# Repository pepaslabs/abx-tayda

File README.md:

# abx-tayda

A relay board for performing blind A/B testing of two audio sources.

This version of the board is designed around parts available from [Tayda electronics](https://www.taydaelectronics.com/).

See the thread at [diyaudio.com](https://www.diyaudio.com/forums/equipment-and-tools/361743-abx-box.html).

This board design is open source hardware, released under the terms of the [MIT license](https://opensource.org/licenses/MIT).  It requires an [ancient version of Kicad](https://archive.org/details/2013-kicad) (sorry, not sorry 😝).  Debian users will need to add a jessie source to install the libpng12 dependency.

## v4.1 release

[schematic](releases/v4.1/abx.pdf)

[gerbers.zip](releases/v4.1/gerbers.zip)

[firmware](https://github.com/pepaslabs/abx-tayda/blob/main/releases/v4.1/firmware/abx/abx.ino)

Changes from v4:
- Include missing base resistor R28.

### Bill of materials

- **D4-6**: three 1N5817 Schottky diodes.
  - Any diode will work, but the lower voltage drop of Schottky diodes extracts more useful life from the 9V battery.
  - [Tayda](https://www.taydaelectronics.com/1n5817-diode-schottky-1a-20v.html)
- **D7-10**: four LED's.
  - Any color.  3mm or 5mm.
  - [Tayda](https://www.taydaelectronics.com/leds/round-leds/5mm-leds/led-5mm-red.html)
- **D11-22**: twelve 1N4148 diodes.
  - Flyback diodes.  Any diode will work here.
  - [Tayda](https://www.taydaelectronics.com/1n4148-switching-signal-diode.html)
- **R1-4**: four 220R 1/4 watt resistors.
  - LED current limiting.  Tune the resistance value to get the LED brightness you prefer.
  - [Tayda](https://www.taydaelectronics.com/resistors/1-4w-metal-film-resistors/resistor-220-ohm-1-4w-1-metal-film-pkg-of-10.html)
- **R5-7,20-22**: six 100k 1/4 watt resistors.
  - Voltage dividers for Arduino inputs.  5% carbon film or 1% metal film.
  - [Tayda](https://www.taydaelectronics.com/resistors/1-4w-metal-film-resistors/10-x-resistor-100k-ohm-1-4w-1-metal-film-pkg-of-10.html)
- **R8-19**: twelve 100k 1/4 watt resistors.
  - MOSFET gate pull-up and pull-down resistors.  5% carbon film or 1% metal film.
  - [Tayda](https://www.taydaelectronics.com/resistors/1-4w-metal-film-resistors/10-x-resistor-100k-ohm-1-4w-1-metal-film-pkg-of-10.html)
- **R23-27**: six 10k 1/4 watt resistors.
  - PNP base current-limiting resistors.  5% carbon film or 1% metal film.
  - [Tayda](https://www.taydaelectronics.com/resistors/1-4w-metal-film-resistors/10-x-resistor-10k-ohm-1-4w-1-metal-film-pkg-of-10.html)
- **SW1-3**: three miniature micro switches.
  - Tayda [MX1382-F91](https://www.taydaelectronics.com/mx1382-f91-micro-switch-1p2t-1a-mx1382-f91.html)
- **Q1,3,5,7,9,11**: six 2N3906 PNP BJT transistors.
  - [Tayda](https://www.taydaelectronics.com/2n3906-general-propose-pnp-transistor.html)
  - Any TO-92 PNP transistor which can handle 100mA (with an EBC pinout) will work fine.
- **Q2,4,6,8,10,12**: six 2N7000 N-channel MOSFETs.
  - [Tayda](https://www.taydaelectronics.com/2n7000-mosfet-n-channel-60v-0-2a.html)
  - Any TO-92 N-channel MOSFET which can handle 100mA (with an SGD pinout) will work fine.
- **K1-6**: six 3V latching relays
  - Tayda [FTR-B3GB003Z](https://www.taydaelectronics.com/ftr-b3gb003z-b10-mini-relay-dpdt-3vdc-1a.html)
- **CON1-3**: three 3.5mm headphone jacks
  - Tayda [PJ-307](https://www.taydaelectronics.com/3-5mm-stereo-enclosed-socket-chassis-jack.html)
  - Digikey [SJ1-3523N](https://www.digikey.com/en/products/detail/cui-devices/SJ1-3523N/738689)
- **IC1**: one Arduino Nano board.
  - Any $5 Arduino Nano board on ebay will work fine.

Choose one:
- **CON4**: 2.1x5.5mm DC barrel jack
  - [Tayda](https://www.taydaelectronics.com/dc-power-jack-2-1mm-barrel-type-pcb-mount.html)
  - [Tayda](https://www.taydaelectronics.com/9v-9-volt-battery-clip-connector-with-barrel-jack-plug.html)
  - [Tayda](https://www.taydaelectronics.com/9v-battery-holder-with-barrel-jack-plug.html)
- **P1**: 9V battery pigtail

## v4 release

[schematic](releases/v4/abx.pdf)

[gerbers.zip](releases/v4/gerbers.zip)

[firmware](https://github.com/pepaslabs/abx-tayda/blob/main/releases/v4/firmware/abx/abx.ino)

Changes from v3:
- Use 2N3906 PNP BJT's which are cheaper than BS250 P-channel MOSFETs (and are available from tayda)
- Use wider traces for the signal path.

## v3 release

[schematic](releases/v3/abx.pdf)

[gerbers.zip](releases/v3/gerbers.zip)

[firmware](https://github.com/pepaslabs/abx-tayda/blob/main/releases/v3/firmware/abx/abx.ino)

Changes from v2:
- Add test points to input X and Y for volume matching convenience.
- Use pins RX0, TX1 instead of A6, A7 (which cannot be used a digital outputs).

## v2 release

This release fixes a couple of bugs from v1:
- Replaced the 100k input resistors with proper voltage dividers.
- Fixed the silkscreen outline of the relays.

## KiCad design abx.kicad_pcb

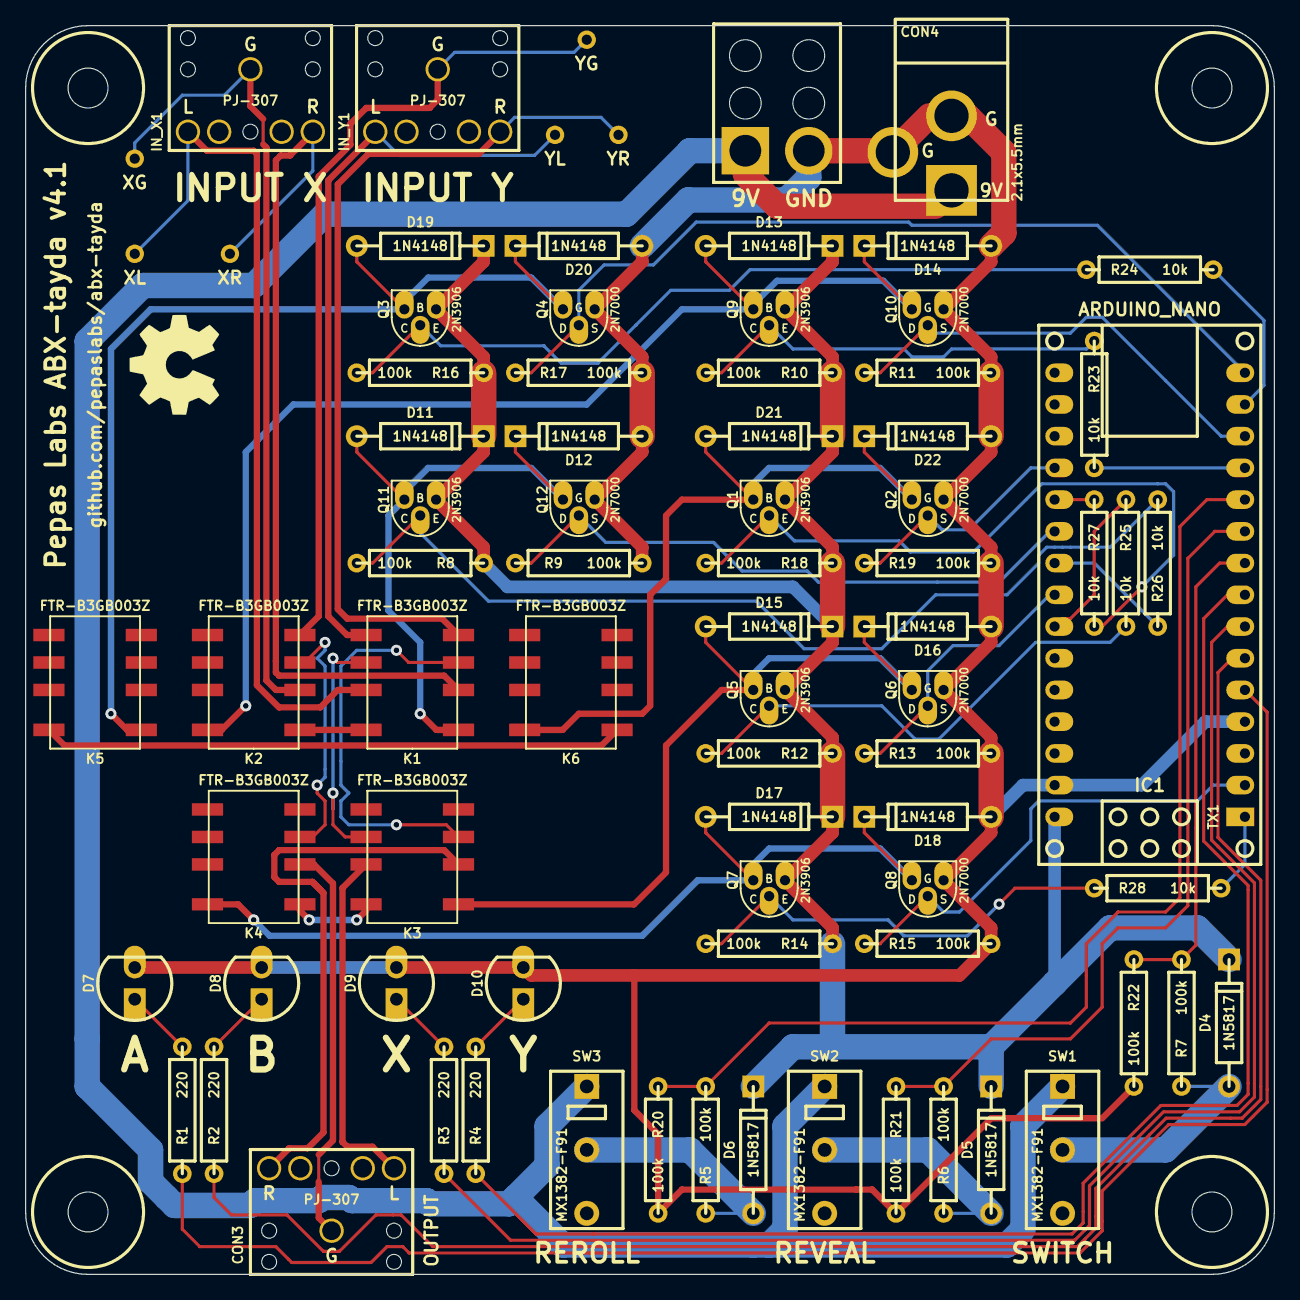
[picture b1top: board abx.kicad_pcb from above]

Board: 2 copper layers, 100.0 x 100.0 mm, 84 parts (0 on the bottom side), 56 nets.

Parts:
CON3: PJ-307; SJ1-3523N
CON4: 2.1x5.5mm; BARREL_JACK_21x55
D4, D5, D6: 1N5817; DIODE_1A_069A_04_PL
D7: LEDA; LED_5MM
D8: LEDB; LED_5MM
D9: LEDX; LED_5MM
D10: LEDY; LED_5MM
D11, D12, D13, D14, D15, D16, D17, D18, D19, D20, D21, D22: 1N4148; DIODE_1A_069A_04_PL
H***: Val**; hole_M3_NPTH
H***#2, H***#3, H***#4: Val**; hole_M3_NPTH
IC1: ARDUINO_NANO; ARDUINO_NANO_PL
IN_X1: PJ-307; SJ1-3523N
IN_Y1: PJ-307; SJ1-3523N
K1, K2, K3, K4, K5, K6: FTR-B3GB003Z; FTR-B3G
P1: CONN_2X1; PIGTAIL2
P2: YL; 1pin_032_058
P3: YR; 1pin_032_058
P4: YG; 1pin_032_058
P5: XL; 1pin_032_058
P6: XR; 1pin_032_058
P7: XG; 1pin_032_058
Q1, Q3, Q5, Q7, Q9, Q11: 2N3906; TO-92_Q_EBC_059Bo_PL
Q2, Q4, Q6, Q8, Q10, Q12: 2N7000; TO-92_Q_SGD_059Bo_PL
R1, R2, R3, R4: 220; R_AXIAL_0W25_059A_PL
R5, R6, R7, R8, R9, R10, R11, R12, R13, R14, R15, R16, R17, R18, R19, R20, R21, R22: 100k; R_AXIAL_0W25_059A_PL
R23, R24, R25, R26, R27, R28: 10k; R_AXIAL_0W25_059A_PL
SW1: SWITCH; MX1382-F91
SW2: REVEAL; MX1382-F91
SW3: REROLL; MX1382-F91

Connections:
5V_LEDA: IC1.5, R1.1
5V_LEDB: IC1.6, R2.1
5V_LEDX: IC1.7, R3.1
5V_LEDY: IC1.8, R4.1
7V: D4.2, D5.2, D6.2, D11.2, D13.2, D15.2, D17.2, D19.2, D21.2, IC1.30, Q1.1, Q3.1, Q5.1, Q7.1, Q9.1, Q11.1, R8.1, R10.1, R12.1, R14.1, R16.1, R18.1
8V_REROLL: D6.1, R5.1, SW3.2
8V_REVEAL: D5.1, R6.1, SW2.2
8V_SWITCH: D4.1, R7.1, SW1.2
9V: CON4.1, P1.1, SW1.1, SW2.1, SW3.1
GND: CON4.2, CON4.3, D7.2, D8.2, D9.2, D10.2, D12.1, D14.1, D16.1, D18.1, D20.1, D22.1, IC1.4, IC1.29, P1.2, Q2.1, Q4.1, Q6.1, Q8.1, Q10.1, Q12.1, R9.2, R11.2, R13.2, R15.2, R17.2, R19.2, R20.2, R21.2, R22.2
unnamed: K3.8, K4.1
unnamed: CON3.3, K3.2
unnamed: CON3.1, K4.2
unnamed: IC1.24, R25.1
unnamed: K5.8, K6.1
unnamed: D9.1, R3.2
unnamed: D8.1, R2.2
unnamed: D7.1, R1.2
unnamed: D10.1, R4.2
unnamed: IN_Y1.3, K1.4, P3.1
unnamed: IN_Y1.1, K2.4, P4.1
unnamed: IC1.9, R7.2, R22.1
unnamed: K1.8, K2.1
unnamed: IC1.10, R6.2, R21.1
unnamed: IC1.14, R24.2
unnamed: IC1.12, R23.2
unnamed: IC1.11, R5.2, R20.1
unnamed: IC1.1, R28.2
unnamed: IN_X1.3, K1.2, P6.1
unnamed: IN_X1.2, K1.7, P5.1
unnamed: IN_Y1.2, K1.5, P2.1
unnamed: CON3.2, K3.7
unnamed: IN_X1.1, K2.2, P7.1
unnamed: IC1.22, R26.1
unnamed: IC1.20, R27.1
unnamed: D15.1, D16.2, K3.1, Q5.3, Q6.3
unnamed: D19.1, D20.2, K5.1, Q3.3, Q4.3
unnamed: D21.1, D22.2, K6.8, Q1.3, Q2.3
unnamed: D11.1, D12.2, K1.1, Q11.3, Q12.3
unnamed: D17.1, D18.2, K4.8, Q7.3, Q8.3
unnamed: D13.1, D14.2, K2.8, Q9.3, Q10.3
NCH1: IC1.13, Q10.2, R11.1
NCH2: IC1.21, Q12.2, R9.1
NCH3: IC1.2, Q8.2, R15.1
NCH4: IC1.23, Q6.2, R13.1
NCH5: IC1.19, Q2.2, R19.1
NCH6: IC1.15, Q4.2, R17.1
PNP1: Q11.2, R8.2, R26.2
PNP2: Q9.2, R10.2, R23.1
PNP3: Q5.2, R12.2, R25.2
PNP4: Q7.2, R14.2, R28.1
PNP5: Q3.2, R16.2, R24.1
PNP6: Q1.2, R18.2, R27.2
RING: K1.3, K3.3
SLEEVE: K2.3, K4.3
TIP: K1.6, K3.6

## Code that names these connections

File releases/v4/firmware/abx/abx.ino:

// ABX switch box (tayda version).
// Copyright 2020 Jason Pepas
// Released under the terms of the MIT license.
// See https://opensource.org/licenses/MIT

// Forum thread:
// https://www.diyaudio.com/forums/equipment-and-tools/361743-abx-box.html


#include <EEPROM.h>


// Pin mapping:

#define LED_A 2
#define LED_B 3
#define LED_X 4
#define LED_Y 5

#define PCH1 A3
#define NCH1 10
#define PCH2 9
#define NCH2 A2
#define PCH3 A5
#define NCH3 0
#define PCH4 1
#define NCH4 A4
#define PCH5 11
#define NCH5 A0
#define PCH6 A1
#define NCH6 12

#define MODE_PIN_REROLL 8
#define MODE_PIN_REVEAL 7
#define MODE_PIN_SWITCH 6


// Misc. constants:

#define MAPPING_A_IS_X 101
#define MAPPING_A_IS_Y 102
#define MAPPING_B_IS_X 102
#define MAPPING_B_IS_Y 101

#define POSITION_X 103
#define POSITION_Y 104

#define RELAY_DURATION 4


// Global variables:

byte g_eeprom_initialized;
byte g_random_seed;
byte g_random_seq;
byte g_abxy_mapping;
byte g_input_position;
byte g_dummy_position;


// EEPROM addresses

#define G_EEPROM_INITIALIZED_ADDR 0
#define G_RANDOM_SEED_ADDR 1
#define G_RANDOM_SEQ_ADDR 2
#define G_ABXY_MAPPING_ADDR 3
#define G_INPUT_POSITION_ADDR 4
#define G_DUMMY_POSITION_ADDR 5


// Misc. functions:

void panic() {
    pinMode(LED_A, OUTPUT);
    pinMode(LED_B, OUTPUT);
    while (true) {
        digitalWrite(LED_A, HIGH);
        digitalWrite(LED_B, HIGH);
    }
}


// EEPROM functions

void load_globals_from_eeprom() {
    g_eeprom_initialized = EEPROM.read(G_EEPROM_INITIALIZED_ADDR);
    if (g_eeprom_initialized != 42) {
        // this is the first time we have ever been run.  initialize all state.
        EEPROM.write(G_EEPROM_INITIALIZED_ADDR, 42);
        EEPROM.write(G_RANDOM_SEED_ADDR, 0);
        EEPROM.write(G_RANDOM_SEQ_ADDR, 0);
        EEPROM.write(G_ABXY_MAPPING_ADDR, MAPPING_A_IS_X);
        EEPROM.write(G_INPUT_POSITION_ADDR, POSITION_X);
        EEPROM.write(G_DUMMY_POSITION_ADDR, POSITION_X);
        disconnect_output_relays();
        set_input_relays_to_x();
        set_dummy_relays_to_x();
        connect_output_relays();
    }

    g_random_seed = EEPROM.read(G_RANDOM_SEED_ADDR);
    g_random_seq = EEPROM.read(G_RANDOM_SEQ_ADDR);
    g_abxy_mapping = EEPROM.read(G_ABXY_MAPPING_ADDR);
    g_input_position = EEPROM.read(G_INPUT_POSITION_ADDR);
    g_dummy_position = EEPROM.read(G_DUMMY_POSITION_ADDR);
}

void store_globals_in_eeprom() {
    EEPROM.write(G_RANDOM_SEED_ADDR, g_random_seed);
    EEPROM.write(G_RANDOM_SEQ_ADDR, g_random_seq);
    EEPROM.write(G_ABXY_MAPPING_ADDR, g_abxy_mapping);
    EEPROM.write(G_INPUT_POSITION_ADDR, g_input_position);
    EEPROM.write(G_DUMMY_POSITION_ADDR, g_dummy_position);
}


// LED functions:

void turn_on_LED(int led) {
    pinMode(led, OUTPUT);
    digitalWrite(led, HIGH);
}

void turn_off_LED(int led) {
    pinMode(led, INPUT);
}


// Relay functions:

void set_input_relays_to_x() {
    pinMode(PCH1, OUTPUT);
    digitalWrite(PCH1, LOW);
    pinMode(NCH1, OUTPUT);
    digitalWrite(NCH1, HIGH);
    delay(RELAY_DURATION);
    pinMode(PCH1, INPUT);
    pinMode(NCH1, INPUT);
    delay(1);
    g_input_position = POSITION_X;
}

void set_input_relays_to_y() {
    pinMode(PCH2, OUTPUT);
    digitalWrite(PCH2, LOW);
    pinMode(NCH2, OUTPUT);
    digitalWrite(NCH2, HIGH);
    delay(RELAY_DURATION);
    pinMode(PCH2, INPUT);
    pinMode(NCH2, INPUT);
    delay(1);
    g_input_position = POSITION_Y;
}

void set_dummy_relays_to_x() {
    pinMode(PCH5, OUTPUT);
    digitalWrite(PCH5, LOW);
    pinMode(NCH5, OUTPUT);
    digitalWrite(NCH5, HIGH);
    delay(RELAY_DURATION);
    pinMode(PCH5, INPUT);
    pinMode(NCH5, INPUT);
    delay(1);
    g_dummy_position = POSITION_X;
}

void set_dummy_relays_to_y() {
    pinMode(PCH6, OUTPUT);
    digitalWrite(PCH6, LOW);
    pinMode(NCH6, OUTPUT);
    digitalWrite(NCH6, HIGH);
    delay(RELAY_DURATION);
    pinMode(PCH6, INPUT);
    pinMode(NCH6, INPUT);
    delay(1);
    g_dummy_position = POSITION_Y;
}

void toggle_input_relays() {
    if (g_input_position == POSITION_X) {
        set_input_relays_to_y();
    } else if (g_input_position == POSITION_Y) {
        set_input_relays_to_x();
    } else {
        panic();
    }
}

void toggle_dummy_relays() {
    if (g_dummy_position == POSITION_X) {
        set_dummy_relays_to_y();
    } else if (g_dummy_position == POSITION_Y) {
        set_dummy_relays_to_x();
    } else {
        panic();
    }
}

void connect_output_relays() {
    pinMode(PCH3, OUTPUT);
    digitalWrite(PCH3, LOW);
    pinMode(NCH3, OUTPUT);
    digitalWrite(NCH3, HIGH);
    delay(RELAY_DURATION);
    pinMode(PCH3, INPUT);
    pinMode(NCH3, INPUT);
    delay(1);
}

void disconnect_output_relays() {
    pinMode(PCH4, OUTPUT);
    digitalWrite(PCH4, LOW);
    pinMode(NCH4, OUTPUT);
    digitalWrite(NCH4, HIGH);
    delay(RELAY_DURATION);
    pinMode(PCH4, INPUT);
    pinMode(NCH4, INPUT);
    delay(1);
}


// Primary functions:

int get_next_random_mapping() {
    int new_mapping;
    // use up to 100 numbers from each seed.
    if (g_random_seq >= 100) {
        g_random_seed++;
        g_random_seq = 0;
    }
    randomSeed(g_random_seed);
    // skip over the previously used numbers from this seed.
    for (int skip=0; skip < g_random_seq; skip++) {
        new_mapping = random(MAPPING_A_IS_X, MAPPING_A_IS_Y+1);
    }
    new_mapping = random(MAPPING_A_IS_X, MAPPING_A_IS_Y+1);
    g_random_seq++;
    return new_mapping;
}

void do_reroll() {
    g_abxy_mapping = get_next_random_mapping();

    bool should_toggle_odd;
    if (g_abxy_mapping == MAPPING_A_IS_X && g_input_position == POSITION_X) {
        should_toggle_odd = false;
    } else if (g_abxy_mapping == MAPPING_A_IS_X && g_input_position == POSITION_Y) {
        should_toggle_odd = true;
    } else if (g_abxy_mapping == MAPPING_B_IS_X && g_input_position == POSITION_X) {
        should_toggle_odd = true;
    } else if (g_abxy_mapping == MAPPING_B_IS_X && g_input_position == POSITION_Y) {
        should_toggle_odd = false;
    } else {
        panic();
    }

    disconnect_output_relays();

    if (should_toggle_odd) {
        toggle_dummy_relays();
        toggle_input_relays();
        toggle_dummy_relays();
    } else {
        toggle_input_relays();
        toggle_dummy_relays();
        toggle_input_relays();
    }

    store_globals_in_eeprom();

    connect_output_relays();

    while (true) {
        turn_on_LED(LED_A);
    }
}

void do_reveal() {
    while (true) {
        if (g_input_position == POSITION_X && g_abxy_mapping == MAPPING_A_IS_X) {
            turn_on_LED(LED_X);
            turn_on_LED(LED_A);
        } else if (g_input_position == POSITION_X && g_abxy_mapping == MAPPING_B_IS_X) {
            turn_on_LED(LED_X);
            turn_on_LED(LED_B);
        } else if (g_input_position == POSITION_Y && g_abxy_mapping == MAPPING_A_IS_Y) {
            turn_on_LED(LED_Y);
            turn_on_LED(LED_A);
        } else if (g_input_position == POSITION_Y && g_abxy_mapping == MAPPING_B_IS_Y) {
            turn_on_LED(LED_Y);
            turn_on_LED(LED_B);
        } else {
            panic();
        }
    }
}

void do_switch() {
    disconnect_output_relays();

    if (g_input_position == POSITION_X) {
        set_input_relays_to_y();
    } else if (g_input_position == POSITION_Y) {
        set_input_relays_to_x();
    } else {
        panic();
    }

    store_globals_in_eeprom();

    connect_output_relays();

    while (true) {
        if (g_input_position == POSITION_X && g_abxy_mapping == MAPPING_A_IS_X) {
            turn_on_LED(LED_A);
        } else if (g_input_position == POSITION_X && g_abxy_mapping == MAPPING_B_IS_X) {
            turn_on_LED(LED_B);
        } else if (g_input_position == POSITION_Y && g_abxy_mapping == MAPPING_A_IS_X) {
            turn_on_LED(LED_B);
        } else if (g_input_position == POSITION_Y && g_abxy_mapping == MAPPING_B_IS_X) {
            turn_on_LED(LED_A);
        } else {
            panic();
        }
    }
}


// Arduino functions:

void setup() {
    // Wait long enough to get past any initial switch bouncing.
    delay(1);

    load_globals_from_eeprom();

    if (digitalRead(MODE_PIN_REROLL)) {
        do_reroll();
    } else if (digitalRead(MODE_PIN_REVEAL)) {
        do_reveal();
    } else if (digitalRead(MODE_PIN_SWITCH)) {
        do_switch();
    } else {
        panic();
    }
}

void loop() {

}

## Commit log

2020-10-31 initial commit (v2)
2020-10-31 v2 board shots
2020-10-31 photo of v1 assembled board
2020-10-31 v2 firmware
2020-11-01 board revision 3
2020-11-01 v3 firmware
2020-11-01 update readme for v3
2020-11-01 v3 board shots
2020-11-04 v4 board shots
2020-11-04 update readme for v4 release
2020-11-17 v4.1 (bugfix)
2020-11-17 4.1 firmware
2020-11-17 readme
2020-11-17 silkscreen fix
2020-11-17 board shots v4.1
